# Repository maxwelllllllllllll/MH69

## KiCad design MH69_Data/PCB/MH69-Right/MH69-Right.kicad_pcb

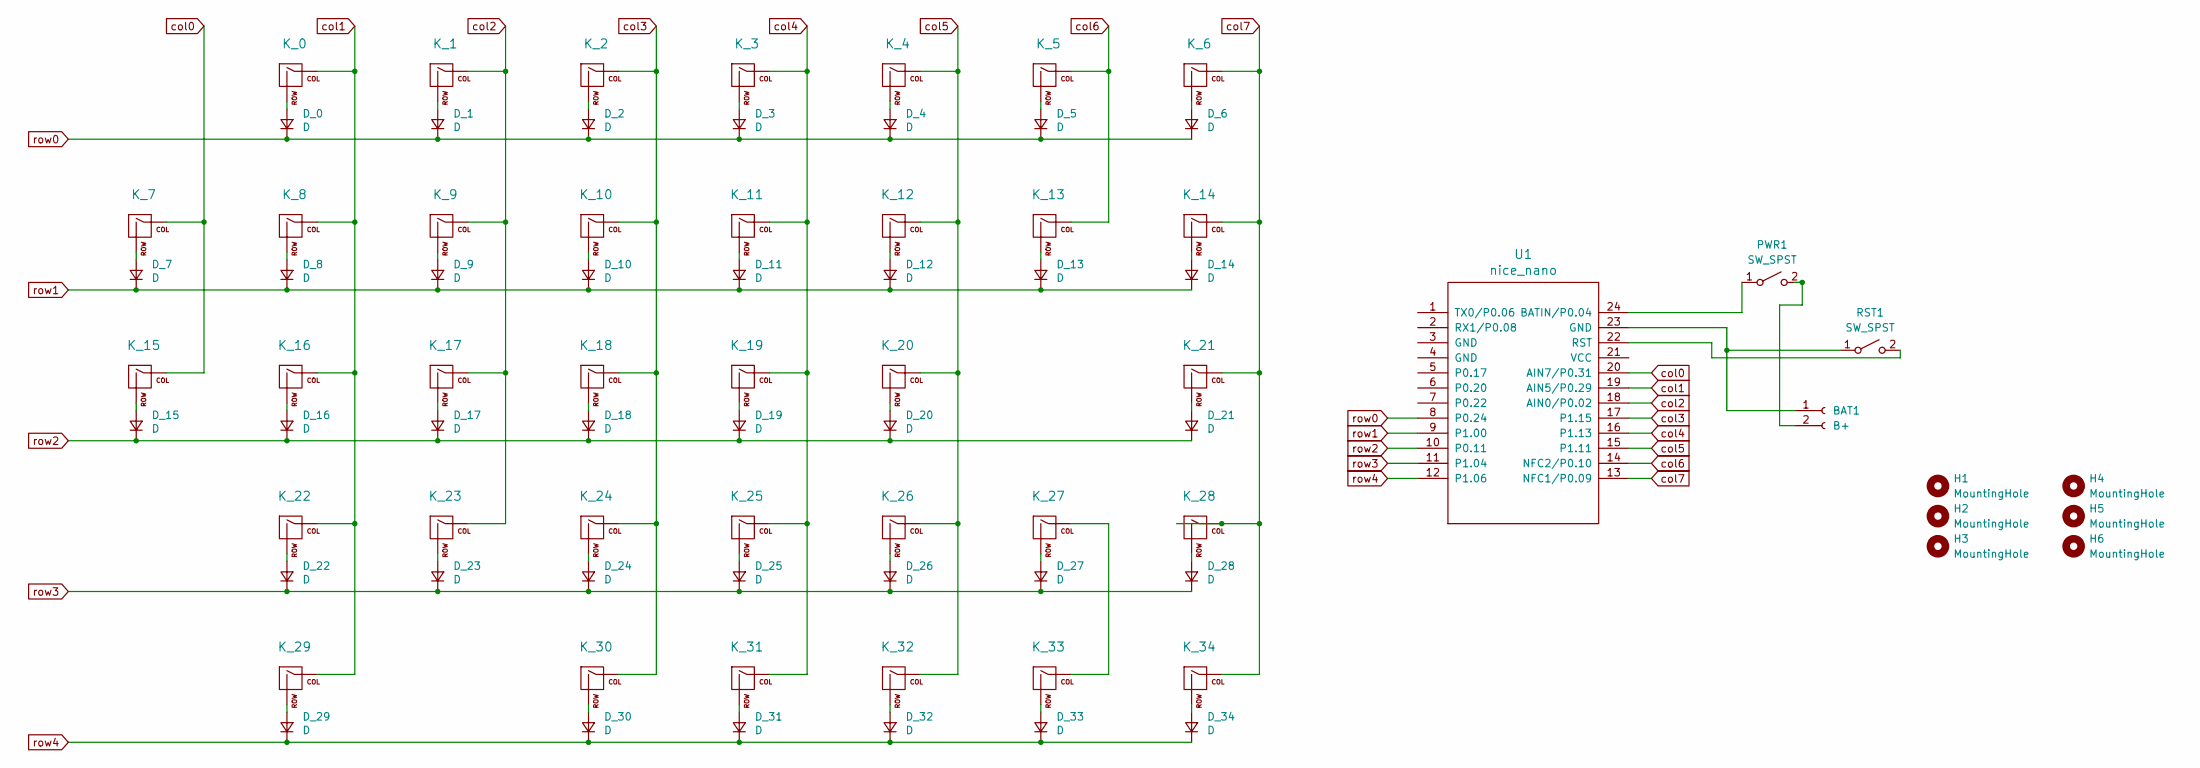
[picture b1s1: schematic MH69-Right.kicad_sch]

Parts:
BAT1: B+; JST_PH_B2B-PH-K_1x02_P2.00mm_Vertical
D_0, D_1, D_2, D_3, D_4, D_5, D_6, D_7, D_8, D_9, D_10, D_11, D_12, D_13, D_14, D_15, D_16, D_17, D_18, D_19, D_20, D_21, D_22, D_23, D_24, D_25, D_26, D_27, D_28, D_29, D_30, D_31, D_32, D_33, D_34: D; Diode_DO-35
H1, H2, H3, H4, H5, H6: MountingHole; MountingHole_3.2mm_M3
K_0, K_1, K_2, K_3, K_4, K_5, K_7, K_8, K_9, K_10, K_11, K_12, K_13, K_14, K_15, K_16, K_17, K_18, K_19, K_20, K_22, K_23, K_24, K_25, K_26, K_27, K_28, K_31, K_32, K_33, K_34: KEYSW; SW_Hotswap_Kailh_Choc_V1_Plated_1.00u
K_6, K_21, K_29, K_30: KEYSW; SW_Hotswap_Kailh_Choc_V1_Plated_1.50u
PWR1: SW_SPST; JST_PH_B2B-PH-K_1x02_P2.00mm_Vertical
RST1: SW_SPST; JST_PH_B2B-PH-K_1x02_P2.00mm_Vertical
U1: nice_nano; nice_nano_no_mid

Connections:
unnamed: BAT1.1, RST1.1 (A), U1.23 (GND)
unnamed: BAT1.2, PWR1.2 (B)
unnamed: D_0.2 (A), K_0.2 (ROW)
unnamed: D_1.2 (A), K_1.2 (ROW)
unnamed: D_2.2 (A), K_2.2 (ROW)
unnamed: D_3.2 (A), K_3.2 (ROW)
unnamed: D_4.2 (A), K_4.2 (ROW)
unnamed: D_5.2 (A), K_5.2 (ROW)
unnamed: D_6.2 (A), K_6.2 (ROW)
unnamed: D_7.2 (A), K_7.2 (ROW)
unnamed: D_8.2 (A), K_8.2 (ROW)
unnamed: D_9.2 (A), K_9.2 (ROW)
unnamed: D_10.2 (A), K_10.2 (ROW)
unnamed: D_11.2 (A), K_11.2 (ROW)
unnamed: D_12.2 (A), K_12.2 (ROW)
unnamed: D_13.2 (A), K_13.2 (ROW)
unnamed: D_14.2 (A), K_14.2 (ROW)
unnamed: D_15.2 (A), K_15.2 (ROW)
unnamed: D_16.2 (A), K_16.2 (ROW)
unnamed: D_17.2 (A), K_17.2 (ROW)
unnamed: D_18.2 (A), K_18.2 (ROW)
unnamed: D_19.2 (A), K_19.2 (ROW)
unnamed: D_20.2 (A), K_20.2 (ROW)
unnamed: D_21.2 (A), K_21.2 (ROW)
unnamed: D_22.2 (A), K_22.2 (ROW)
unnamed: D_23.2 (A), K_23.2 (ROW)
unnamed: D_24.2 (A), K_24.2 (ROW)
unnamed: D_25.2 (A), K_25.2 (ROW)
unnamed: D_26.2 (A), K_26.2 (ROW)
unnamed: D_27.2 (A), K_27.2 (ROW)
unnamed: D_28.2 (A), K_28.2 (ROW)
unnamed: D_29.2 (A), K_29.2 (ROW)
unnamed: D_30.2 (A), K_30.2 (ROW)
unnamed: D_31.2 (A), K_31.2 (ROW)
unnamed: D_32.2 (A), K_32.2 (ROW)
unnamed: D_33.2 (A), K_33.2 (ROW)
unnamed: D_34.2 (A), K_34.2 (ROW)
unnamed: K_27.1 (COL), K_33.1 (COL)
unnamed: PWR1.1 (A), U1.24 (BATIN/P0.04)
unnamed: RST1.2 (B), U1.22 (RST)
col0: K_7.1 (COL), K_15.1 (COL), U1.20 (AIN7/P0.31)
col1: K_0.1 (COL), K_8.1 (COL), K_16.1 (COL), K_22.1 (COL), K_29.1 (COL), U1.19 (AIN5/P0.29)
col2: K_1.1 (COL), K_9.1 (COL), K_17.1 (COL), K_23.1 (COL), U1.18 (AIN0/P0.02)
col3: K_2.1 (COL), K_10.1 (COL), K_18.1 (COL), K_24.1 (COL), K_30.1 (COL), U1.17 (P1.15)
col4: K_3.1 (COL), K_11.1 (COL), K_19.1 (COL), K_25.1 (COL), K_31.1 (COL), U1.16 (P1.13)
col5: K_4.1 (COL), K_12.1 (COL), K_20.1 (COL), K_26.1 (COL), K_32.1 (COL), U1.15 (P1.11)
col6: K_5.1 (COL), K_13.1 (COL), U1.14 (NFC2/P0.10)
col7: K_6.1 (COL), K_14.1 (COL), K_21.1 (COL), K_28.1 (COL), K_34.1 (COL), U1.13 (NFC1/P0.09)
row0: D_0.1 (K), D_1.1 (K), D_2.1 (K), D_3.1 (K), D_4.1 (K), D_5.1 (K), D_6.1 (K), U1.8 (P0.24)
row1: D_7.1 (K), D_8.1 (K), D_9.1 (K), D_10.1 (K), D_11.1 (K), D_12.1 (K), D_13.1 (K), D_14.1 (K), U1.9 (P1.00)
row2: D_15.1 (K), D_16.1 (K), D_17.1 (K), D_18.1 (K), D_19.1 (K), D_20.1 (K), D_21.1 (K), U1.10 (P0.11)
row3: D_22.1 (K), D_23.1 (K), D_24.1 (K), D_25.1 (K), D_26.1 (K), D_27.1 (K), D_28.1 (K), U1.11 (P1.04)
row4: D_29.1 (K), D_30.1 (K), D_31.1 (K), D_32.1 (K), D_33.1 (K), D_34.1 (K), U1.12 (P1.06)

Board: 2 copper layers, 80 parts (38 on the bottom side), 53 nets, no tracks yet.

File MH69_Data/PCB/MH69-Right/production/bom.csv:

Designator,Footprint,Quantity,Value,LCSC Part #
BAT1,JST_PH_B2B-PH-K_1x02_P2.00mm_Vertical,1,B-,
"D_0, D_1, D_10, D_11, D_12, D_13, D_14, D_15, D_16, D_17, D_18, D_19, D_2, D_20, D_21, D_22, D_23, D_24, D_25, D_26, D_27, D_28, D_29, D_3, D_30, D_31, D_32, D_33, D_34, D_4, D_5, D_6, D_7, D_8, D_9",Diode_DO-35,35,D,
"K_0, K_1, K_10, K_11, K_12, K_13, K_14, K_15, K_16, K_17, K_18, K_19, K_2, K_20, K_22, K_23, K_24, K_25, K_26, K_27, K_28, K_3, K_31, K_32, K_33, K_34, K_37, K_4, K_5, K_7, K_8, K_9",Choc-MX-19mm-1u,32,KEYSW,
"K_21, K_29, K_30, K_36, K_39, K_6",Choc-MX-19mm-1.5u,6,KEYSW,
"K_35, K_38",Choc-MX-19mm-2u,2,KEYSW,
K_40,Choc-MX-19mm-2.25u,1,KEYSW,
K_41,Choc-MX-19mm-1.75u,1,KEYSW,
"PWR1, RST1",JST_PH_B2B-PH-K_1x02_P2.00mm_Vertical,2,SW_SPST,
U1,nice_nano_no_mid,1,nice_nano,

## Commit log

2025-01-18 Adding all of CB files
2025-01-18 Updating Directories
2025-01-19 Initial PCB file additions
2025-01-19 Images
2025-01-19 Added Kailh Plated 1Us to Left
2025-01-19 some kicad work
2025-01-20 Left side layout progress
2025-01-20 updated left number row
2025-01-20 tiny change to a single diode
2025-01-20 closed Kicad
2025-01-22 very minor layout tweaking
2025-01-23 fine touches on edge cuts mostly
2025-01-23 dunno
2025-01-23 Added Scotto Stuff
2025-01-23 Updated some libs
2025-01-24 Updated footprint
2025-01-24 updated diode locations
2025-01-26 completed left side diode placement
2025-01-26 started left routing
2025-01-27 completed all routing for left except power etc
2025-01-27 Nothing much
2025-01-27 THE BIG CHANGE - schematic and PCB layout
2025-01-28 Left side finished?
2025-01-29 Finished Left and moving on to Right
2025-01-29 Footprint Lib Move
2025-02-14 I dunno
